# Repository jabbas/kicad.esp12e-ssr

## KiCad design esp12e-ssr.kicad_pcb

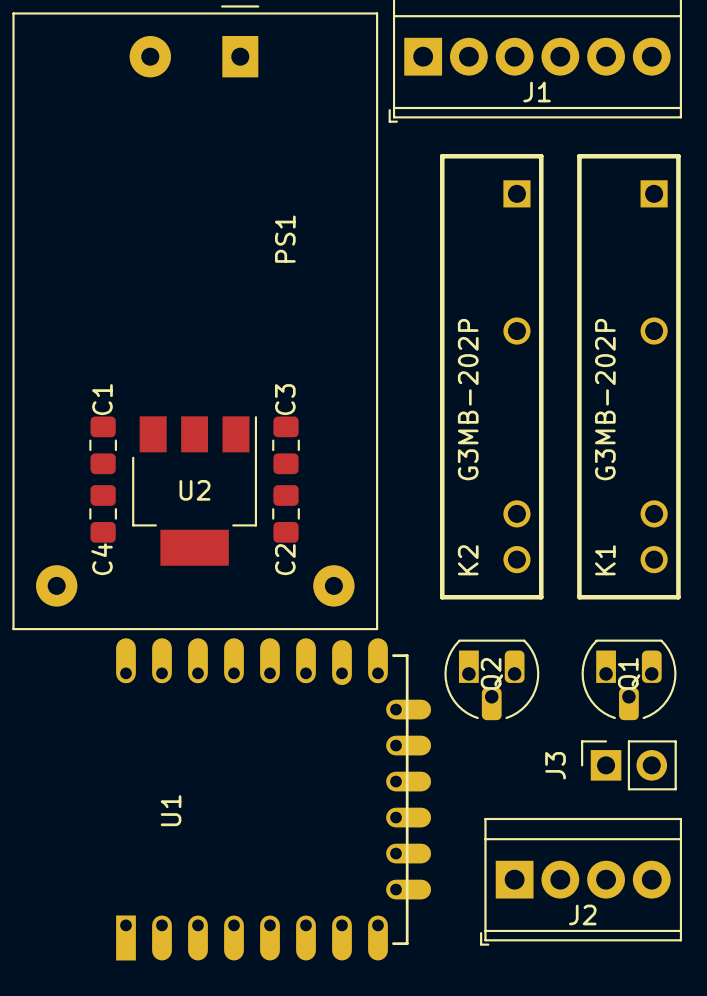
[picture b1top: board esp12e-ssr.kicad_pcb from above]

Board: 2 copper layers, 14 parts (0 on the bottom side), 13 nets, no tracks yet.

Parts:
C1, C3: 1uF; C_0805_2012Metric_Pad1.15x1.40mm_HandSolder
C2, C4: 4.7uF; C_0805_2012Metric_Pad1.15x1.40mm_HandSolder
J1: 230V Terminal; TerminalBlock_TE_282834-6_1x06_P2.54mm_Horizontal
J2: Switch Terminal; TerminalBlock_TE_282834-4_1x04_P2.54mm_Horizontal
J3: 5V AUX; PinSocket_1x02_P2.54mm_Vertical
K1, K2: G3MB-202P; RELAY_G3MB-202P
PS1: HLK-PM01; Converter_ACDC_HiLink_HLK-PMxx
Q1, Q2: BC547; TO-92_HandSolder
U1: ESP-12E
U2: AMS1117-3.3; SOT-223-3_TabPin2

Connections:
+3.3V: C2.1, C3.1, U1.8, U2.2
+5V: C1.1, C4.1, J3.2, K1.3, K2.3, PS1.4, U2.3
AC: J1.2, J1.4, J1.6, PS1.1
GND: C1.2, C2.2, C3.2, C4.2, J2.2, J2.3, J3.1, PS1.3, Q1.3, Q2.3, U1.9, U2.1
GNDREF: J1.3, K1.2, K2.2, PS1.2
unnamed: J1.1, K1.1
unnamed: J1.5, K2.1
unnamed: J2.1, U1.7
unnamed: J2.4, U1.6
unnamed: K1.4, Q1.1
unnamed: K2.4, Q2.1
unnamed: Q1.2, U1.14
unnamed: Q2.2, U1.13
